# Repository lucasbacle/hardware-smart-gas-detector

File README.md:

# MOSH Project: Smart gas detector
KiCad schematic and pcb layout for a smart gas detector using a cutting edge nanoparticles-based sensor and LoRaWAN connectivity. Due to time constraints, we only proceeded with the routing of an expansion board which connect to the main detector for it to use our sensor instead of the commercial ones.

## Smart gaz detector
A battery-operated, LoRaWAN-connected, Volatile Organic Compounds (VOC), temperature and humidity sensor. This device could monitor the indoor air quality and trigger an alarm, both on site with its loud piezo and remotly via a LoRaWAN network. The LiPo battery can be recharged with an usual usb charger. 

### Schematic

### PCB (WIP)
Due to the complexity of routing a 4-layer pcb with RF, analog signals & switching power supplies, we were not able to finish the routing but started to place the component according to manufacturer's recommended layouts.

## Expansion board
Being powered by a relatively small 1-cell LiPo battery, we made the choice not to use the nano-particles based sensor in our device. Indeed, it requires relatively high voltage which would induces more complex circuitry. This expansion board lets the detector use this sensor. Including the conditionner circuit, an external power source can be connected.

### Schematic

### PCB

| Front side  | Bottom side |
| ------------- | ------------- |
 |

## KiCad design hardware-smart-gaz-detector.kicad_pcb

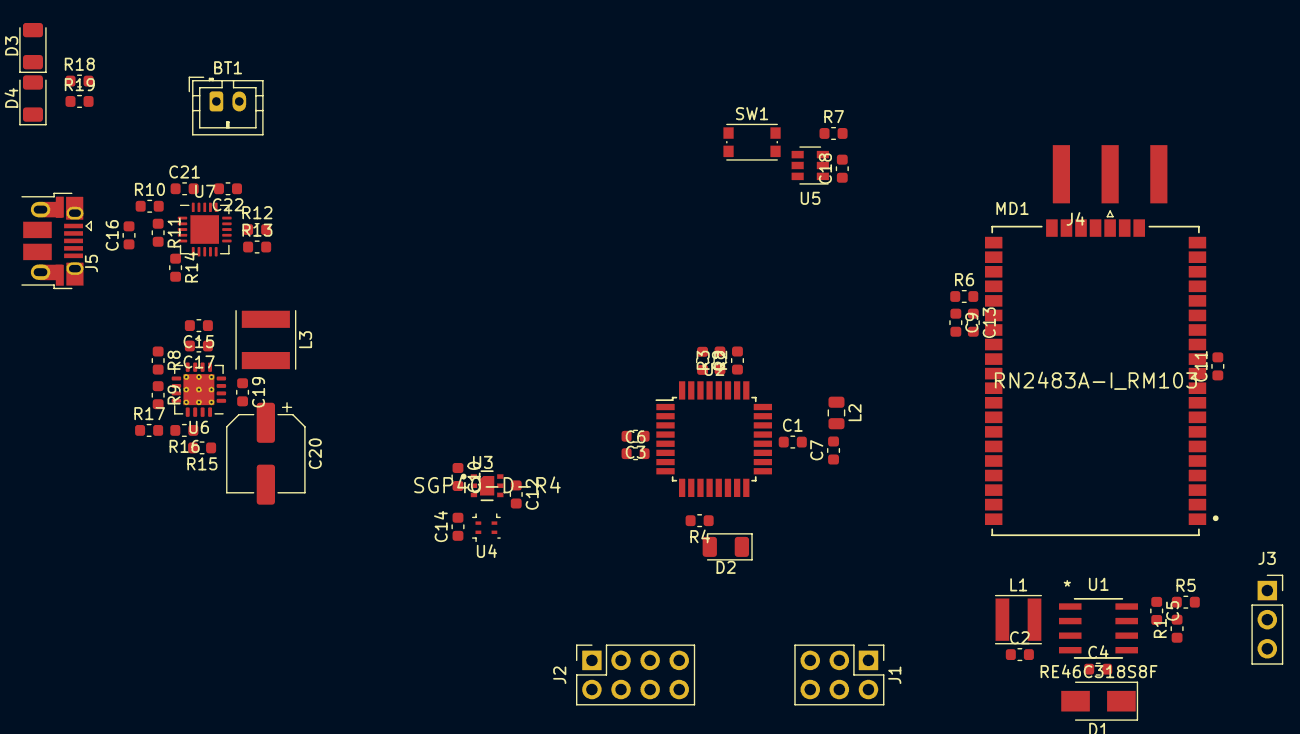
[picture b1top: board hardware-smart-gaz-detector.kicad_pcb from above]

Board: 4 copper layers, 63 parts (0 on the bottom side), 44 nets, no tracks yet.

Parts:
BT1: 1c LiPo; JST_PH_B2B-PH-K_1x02_P2.00mm_Vertical
C1, C6, C7, C8, C11, C13, C14, C17, C18: 100n; C_0603_1608Metric
C2, C4, C15, C16, C21, C22: 10µ; C_0603_1608Metric
C3, C9: 4.7µ; C_0603_1608Metric
C5: 1n; C_0603_1608Metric
C10, C12: 1µ; C_0603_1608Metric
C19: 2.2µ; C_0603_1608Metric
C20: 100µ; CP_Elec_6.3x5.8
D1: D_Schottky; D_SMA
D2: LED; LED_1206_3216Metric
D3: ORANGE; LED_1206_3216Metric
D4: GREEN; LED_1206_3216Metric
J1: Conn_ICSP; PinHeader_2x03_P2.54mm_Vertical
J2: Conn_Extension; PinSocket_2x04_P2.54mm_Vertical
J3: Conn_Piezo; PinSocket_1x03_P2.54mm_Vertical
J4: SMA; SMA_Amphenol_132289_EdgeMount
J5: USB_B_Mini; USB_Micro-B_Amphenol_10103594-0001LF_Horizontal
L1: 10µ; L_Taiyo-Yuden_MD-4040
L2: 10µ; L_0805_2012Metric
L3: 6.8µ; L_Taiyo-Yuden_MD-5050
MD1: RN2483A-I_RM103; Microchip-RN2483A-I_RM103-0-0-MFG
R1: 1.5M; R_0603_1608Metric
R2, R3: 4.7k; R_0603_1608Metric
R4: 10; R_0603_1608Metric
R5, R16: 200k; R_0603_1608Metric
R6, R13: 100k; R_0603_1608Metric
R7: 22k; R_0603_1608Metric
R8: 1.87M; R_0603_1608Metric
R9: 340k; R_0603_1608Metric
R10: 330k; R_0603_1608Metric
R11: 110k; R_0603_1608Metric
R12, R18, R19: 1k; R_0603_1608Metric
R14: 15k; R_0603_1608Metric
R15: 1.1M; R_0603_1608Metric
R17: 1M; R_0603_1608Metric
SW1: SW_Push; SW_Push_1P1T_NO_CK_KMR2
U1: RE46C318S8F
U2: ATmega328P-AU; TQFP-32_7x7mm_P0.8mm
U3: SGP40-D-R4; Sensirion-SGP40-D-R4-MFG
U4: SHT4x; WDFN-4_1.5x1.5_Pitch0.8mm
U5: TPL5010; SOT-23-6
U6: TPS61090; Texas_S-PVQFN-N16_EP2.7x2.7mm_ThermalVias
U7: MCP73871-2AA; QFN-20-1EP_4x4mm_P0.5mm_EP2.5x2.5mm

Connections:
+3.3VA: C7.2, L2.2, U2.18
+3V3: C2.1, C3.1, C6.2, C9.2, C10.1, C11.2, C12.1, C13.2, C14.2, C18.1, C19.2, C20.1, J1.4, J2.1, L1.1, L2.1, MD1.12, MD1.34, R2.2, R3.2, R6.1, R15.1, R17.1, SW1.2, U1.2, U2.4, U2.6, U3.1, U3.5, U4.3, U5.1, U6.1, U6.15, U6.16
+10V: C4.2, D1.1, U1.5
+BATT: C15.2, C17.2, C21.2, L3.1, R8.1, U6.8, U6.11, U7.1, U7.20
ADC0: J2.7, U2.23
ADC1: J2.6, U2.24
GND: BT1.2, C1.2, C2.2, C3.2, C4.1, C6.1, C7.1, C8.1, C9.1, C10.2, C11.1, C12.2, C13.1, C14.1, C15.1, C16.1, C17.1, C18.2, C19.1, C20.2, C21.1, C22.1, D2.1, J1.6, J2.8, J4.2, J5.5, MD1.1, MD1.8, MD1.11, MD1.20, MD1.21, MD1.22, MD1.24, MD1.26, MD1.27, MD1.28, MD1.33, MD1.41, MD1.47, R7.2, R9.2, R11.2, R12.2, R13.2, R14.2, R16.2, U1.4, U2.3, U2.5, U2.21, U3.2, U3.4, U3.7, U4.4, U5.2, U6.5, U6.6, U6.7, U6.10, U6.13, U6.17, U7.10, U7.11, U7.21
GPIO_Done: U2.2, U5.4
GPIO_Horn: U1.8, U2.1
GPIO_LBO: R17.2, U2.32, U6.12
I2C_SCL: J2.2, R3.1, U2.28, U3.6, U4.2
I2C_SDA: J2.3, R2.1, U2.27, U3.3, U4.1
unnamed: BT1.1, C22.2, U7.14, U7.15, U7.16
unnamed: C1.1, U2.20
unnamed: C5.1, R1.2, R5.1, U1.1
unnamed: D1.2, L1.2, U1.3
unnamed: D2.2, R4.1
unnamed: D3.1, R18.1
unnamed: D4.1, R19.1
unnamed: J4.1, MD1.23
unnamed: L3.2, U6.3, U6.4
unnamed: R7.1, SW1.1, U5.3
unnamed: R8.2, R9.1, U6.9
unnamed: R10.2, R11.1, U7.2
unnamed: R12.1, U7.13
unnamed: R13.1, U7.12
unnamed: R14.1, U7.5
unnamed: R15.2, R16.1, U6.14
unnamed: R18.2, U7.8
unnamed: R19.2, U7.7
PCINT0_Wake: U2.12, U5.5
PWM0A_Led: R4.2, U2.10
PWM0B: J2.4, U2.9
RN2483_nRST: MD1.32, R6.2, U2.11
SPI_MISO: J1.1, U2.16
SPI_MOSI: J1.5, U2.15
SPI_SCK: J1.2, U2.17
UART0_RX: MD1.6, U2.30
UART0_TX: MD1.7, U2.31
VBUS: C16.2, D3.2, D4.2, J5.1, R10.1, U7.3, U7.4, U7.9, U7.17, U7.18, U7.19
nRST: C8.2, J1.3, U2.29, U5.6
piezo_feedback: J3.1, R5.2
piezo_gnd: J3.3, R1.1, U1.6
piezo_input: C5.2, J3.2, U1.7

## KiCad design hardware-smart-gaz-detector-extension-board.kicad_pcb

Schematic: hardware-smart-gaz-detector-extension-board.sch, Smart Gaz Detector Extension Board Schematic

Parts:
C1, C2, C4, C5: 100n; C_0603_1608Metric
C3: 10µ; CP_Elec_5x5.4
C6: 1µ; C_0603_1608Metric
J1: Conn_Extension; PinSocket_2x04_P2.54mm_Vertical
J2: Jack-DC; BarrelJack_Horizontal
Q1: FDN327N; ON_Semi-527AG-01-12_2008-O-0; mouser part number 512-FDN327N; digikey description MOSFET N-CH 20V 2A SSOT-3
R1, R3: 10k; R_0603_1608Metric
R2: 250; R_0603_1608Metric
R4: 100k; R_0603_1608Metric
R5, R7: 1k; R_0603_1608Metric
R6: 50k; R_0603_1608Metric
U1: aime_gaz_sensor; TO-5-10_Window
U2: LTC2050HVCS5TRPBF; Linear_Technology-LTC2050HVCS5TRPBF-Level_B
U3: MCP4017-xxxxLT; SOT-363_SC-70-6

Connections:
+3V3: C2.2, C5.2, J1.3, U1.1, U1.6, U2.5, U3.1
+12V: C3.1, J1.2, J2.1, Q1.3
ADC0_Gaz: C4.2, J1.7, R5.2
ADC1_Temperature: J1.5, R1.2, U1.4
GND: C1.2, C2.1, C3.2, C4.1, C5.1, J1.4, J2.2, R1.1, R4.1, R7.1, U1.8, U1.9, U1.10, U2.2, U3.2
I2C_SCL: J1.6, U3.3
I2C_SDA: J1.8, U3.4
unnamed: C1.1, R3.1, R4.2, U2.3
unnamed: Q1.1, R2.2
unnamed: Q1.2, U1.5
unnamed: R6.2, U3.6
PWM_PolySi: J1.1, R2.1
aop_-: C6.1, R7.2, U2.4, U3.5
aop_out: C6.2, R5.1, R6.1, U2.1
u_gaz: R3.2, U1.7

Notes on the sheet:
Extension board

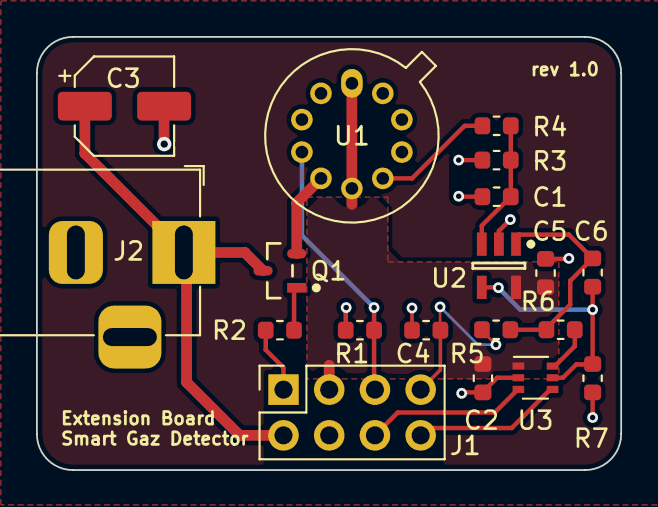
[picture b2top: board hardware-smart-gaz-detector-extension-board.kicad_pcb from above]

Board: 2 copper layers, 32.5 x 24.1 mm, 19 parts (0 on the bottom side), 15 nets.

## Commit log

2020-11-23 add important datasheets
2020-11-23 add base kicad project
2020-11-24 update schematic
2020-12-02 version 0.2
2021-01-16 final commit before portfolio
2021-01-16 add 3d view
2021-01-16 Update README.md
    Fix typo
2021-01-17 add aime gaz sensor datasheet
2021-01-17 update aime gaz sensor datasheet
2021-01-17 update lib table

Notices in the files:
parts and their libraries:
Copyright 2016 Accelerated Designs. All rights reserved.
